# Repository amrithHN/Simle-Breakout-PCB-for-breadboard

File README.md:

# Simle-Breakout-PCB-for-breadboard

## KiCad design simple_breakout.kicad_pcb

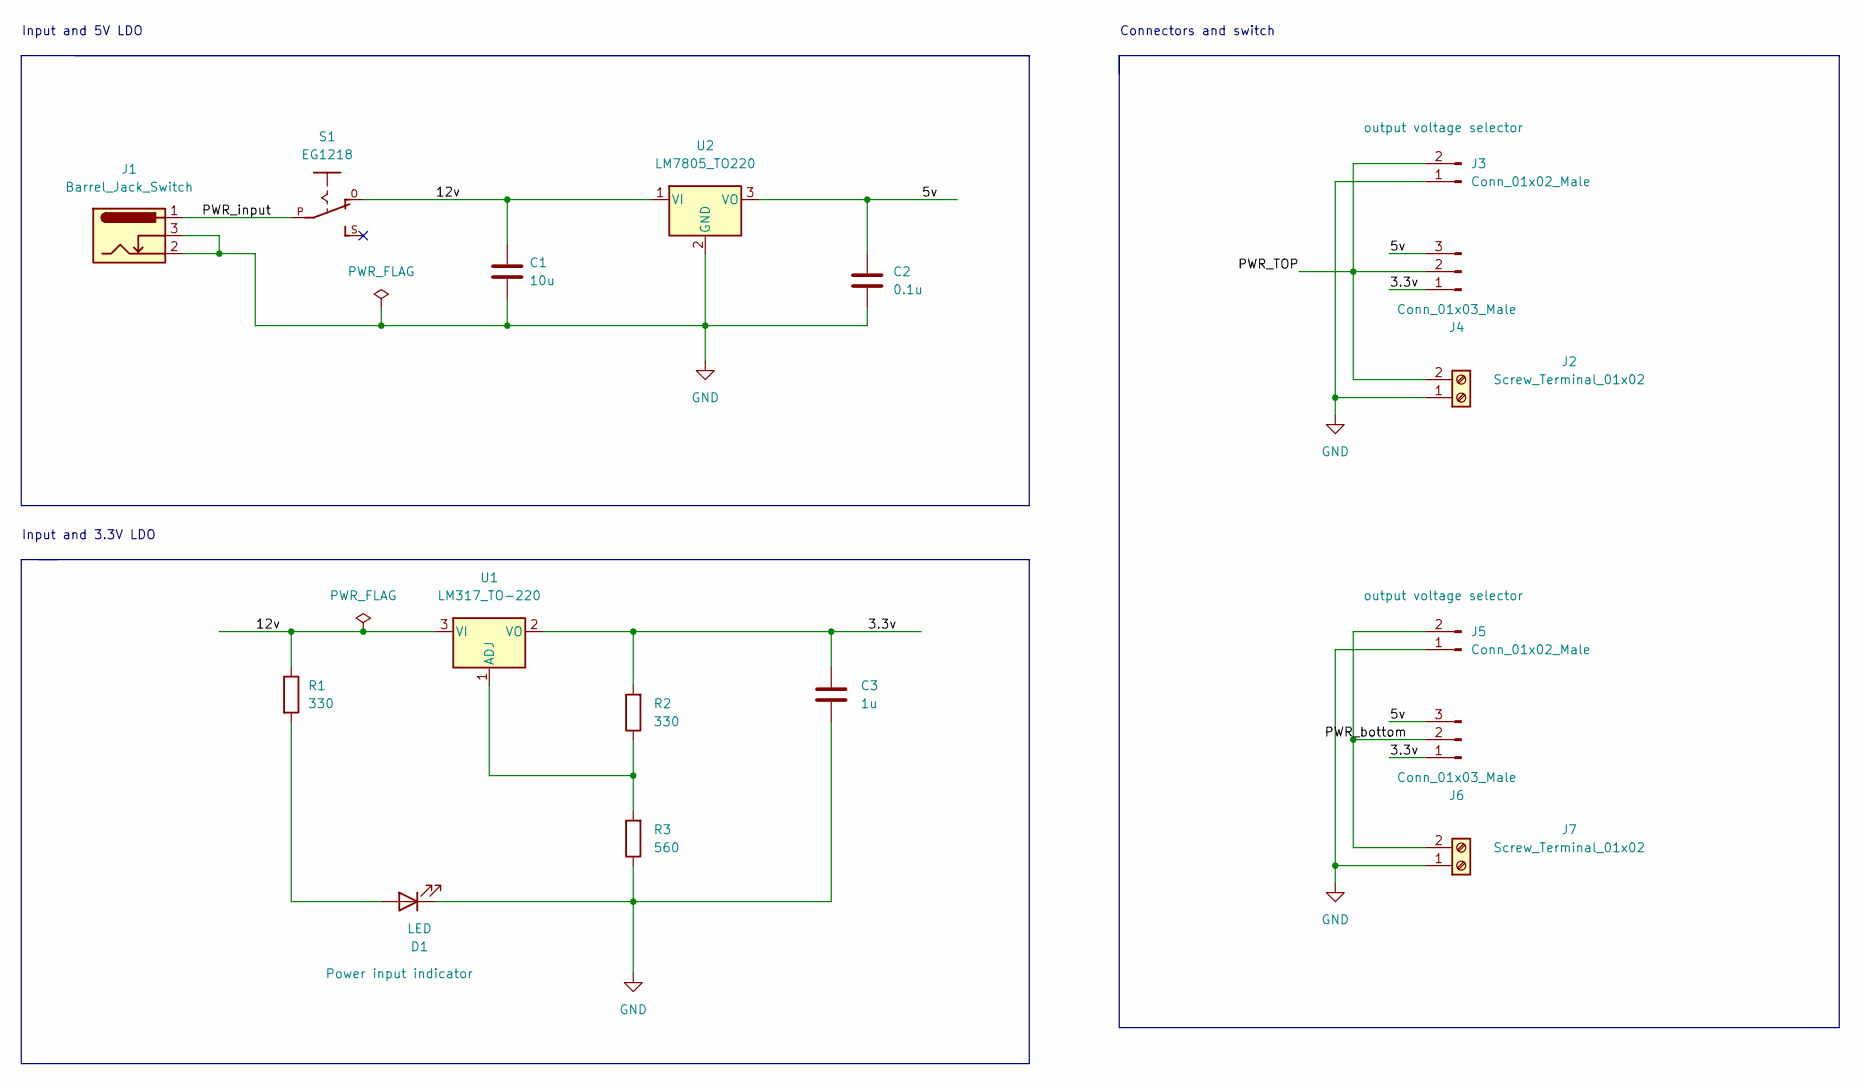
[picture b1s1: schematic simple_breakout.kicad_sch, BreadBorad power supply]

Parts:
C1: 10u; C_Disc_D3.0mm_W1.6mm_P2.50mm
C2: 0.1u; C_Disc_D3.0mm_W1.6mm_P2.50mm
C3: 1u; C_Disc_D3.0mm_W1.6mm_P2.50mm
D1: LED; LED_D5.0mm
J1: Barrel_Jack_Switch; BarrelJack_Horizontal
J2, J7: Screw_Terminal_01x02; TerminalBlock_bornier-2_P5.08mm
J3, J5: Conn_01x02_Male; PinHeader_1x02_P2.54mm_Vertical
J4, J6: Conn_01x03_Male; PinHeader_1x03_P2.54mm_Vertical
R1, R2: 330; R_Axial_DIN0204_L3.6mm_D1.6mm_P7.62mm_Horizontal
R3: 560; R_Axial_DIN0204_L3.6mm_D1.6mm_P7.62mm_Horizontal
S1: EG1218
U1: LM317_TO-220; TO-220-3_Vertical
U2: LM7805_TO220; TO-220-3_Vertical

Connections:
/3.3v: C3.2, J4.1, J6.1, R2.2, U1.2 (VO)
/5v: C2.1, J4.3, J6.3, U2.3 (VO)
/12v: C1.1, R1.1, S1.O, U1.3 (VI), U2.1 (VI)
/PWR_TOP: J2.2, J3.2, J4.2
/PWR_bottom: J5.2, J6.2, J7.2
/PWR_input: J1.1, S1.P
GND: C1.2, C2.2, C3.1, D1.1 (K), J1.2, J1.3, J2.1, J3.1, J5.1, J7.1, R3.1, U2.2 (GND)
unnamed: D1.2 (A), R1.2
unnamed: R2.1, R3.2, U1.1 (ADJ)

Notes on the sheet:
Input and 3.3V LDO
Connectors and switch
Input and 5V LDO

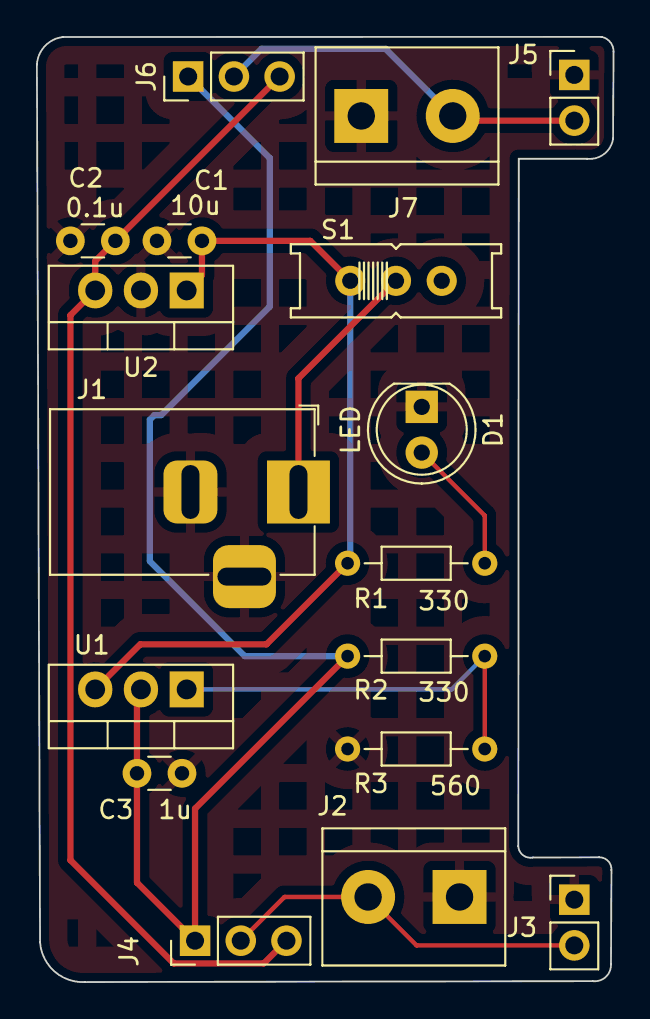
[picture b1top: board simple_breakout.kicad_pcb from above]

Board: 2 copper layers, 32.0 x 52.5 mm, 17 parts (0 on the bottom side), 9 nets.

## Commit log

2022-06-16 other files
2022-06-16 added image
